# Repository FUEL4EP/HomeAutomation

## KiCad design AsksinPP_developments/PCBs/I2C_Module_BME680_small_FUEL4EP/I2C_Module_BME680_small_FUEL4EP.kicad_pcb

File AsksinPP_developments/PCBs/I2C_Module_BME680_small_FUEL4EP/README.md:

# I2C_Module_BME680_small_FUEL4EP  

## kleine I2C BME680 VOC Sensor Aufsteckplatine für DIY AsksinPP-Projekte

- basierend auf [Bosch BME680](https://www.bosch-sensortec.com/media/boschsensortec/downloads/datasheets/bst-bme680-ds001.pdf)
- passend zu den folgenden Mutterplatinen:
	* [HB_Stamp_ATMega1284P_FUEL4EP](https://github.com/FUEL4EP/HomeAutomation/tree/master/AsksinPP_developments/PCBs/HB_Stamp_ATMega1284P_FUEL4EP)	
- VCC max. ist 3,3 Volt !!
- die voreingestellte Standard-I2C-Adresse ist 0x76
- für die I2C-Adresse 0x77 ist der Jumper JP2 aufzutrennen und der Jumper JP1 mit Lötzinn zu überbrücken

- Infos zu AsksinPP sind [hier](https://asksinpp.de) und [hier](https://asksinpp.de/Grundlagen/01_hardware.html#verdrahtung) zu finden

## Platinenmaße

- Breite: 14,08 mm
- Weite: 17 mm
- Platinendicke 1,6 mm (bei der Bestellung bei JLCPCB auswählen)

## Stromlaufplan

- ist [hier](./Schematics/I2C_Module_BME680_small_FUEL4EP.pdf)

## Status

- die Platine V1.0 wurde bei JLCPCB gefertigt und mit dem Sketch [HB-UNI-SENSOR1-AQ-BME680_KF_rLF](https://github.com/FUEL4EP/HomeAutomation/tree/master/AsksinPP_developments/sketches/HB-UNI-Sensor1-AQ-BME680_KF_rLF) validiert:

## Rückmeldungen

- und Verbesserungsvorschläge sind willkommen.

### KiCAD Plugin
- für die Erzeugung der JLCPCB Produktionsdaten wurde das Plugin [KiCAD JLCPCB tools](https://github.com/bouni/kicad-jlcpcb-tools) verwendet.

## Daten für die Bestellung bei JLCPCB

- die Daten für die Bestellung liegen im Verzeichnis [./jlcpcb/production_files/](./jlcpcb/production_files/)
- Gerber-Daten als Zip-Datei
- BOM- und CPL-Daten als CSV-Datei

## lokale Installation des Github Releases auf Deinem Computer

- gehe bitte in Dein Zielinstallationsverzeichnis, wo Du mit der I2C_Module_BME680_small_FUEL4EP Platine mit KiCAD arbeiten möchtest

  - gebe dort 'git clone https://github.com/FUEL4EP/HomeAutomation.git' ein
	  + damit lädst Du mein [Sammelrepository](https://github.com/FUEL4EP/HomeAutomation) für alle meine auf Github freigegebenen HomeBrew Entwicklungen herunter.
  - dann findest Du ein neues Verzeichnis 'HomeAutomation' auf Deinem Rechner, das alle meine auf Github freigebenen Entwicklungen enthält, siehe [README.md](https://github.com/FUEL4EP/HomeAutomation/blob/master/README.md)
  	+ mache bitte regelmäßig ein Update mit 'git pull'
 -	die Platine I2C_Module_BME680_small_FUEL4EP findest Du unter './HomeAutomation/tree/master/AsksinPP_developments/PCBs/I2C_Module_BME680_small_FUEL4EP'
 
- alternativ kann vom Github [Sammelrepository](https://github.com/FUEL4EP/HomeAutomation) die ZIP-Datei HomeAutomation-master.zip heruntergeladen und auf dem lokalen Rechner ausgepackt werden. Bitte dann regelmäßig auf Github nach Updates schauen.

## Versionsverlauf

- V1.0   29. Sep 2024: Initiale Veröffentlichung auf Github
- L V1.1 30. Sep 2024: Verbesserte Platzierung von C3
- KiCad Schaltplan-Editor Version: 8.0.5-8.0.5-0~ubuntu22.04.1, release build
 unter Kubuntu22.04.4
- KiCad Leiterplatteneditor Version: 8.0.5-8.0.5-0~ubuntu22.04.1, release build
 unter Kubuntu22.04.4
- PCB Version 1.1
- Schematics  1.0

## Sammelbestellung

- wer Interesse an einer gemeinsamen Bestellung von Platinen und/oder Gehäusen bei JLCPCB hat, fragt bitte per per PN bei bei [FUEL4EP](https://homematic-forum.de/forum/ucp.php?i=pm&mode=compose&u=20685) an.
- wenn genügend Interesse (>= 20 bestückte Platinen und/oder 3D gedruckten Gehäusen) zustande kommt, biete ich an, Platinen  und Gehäuse gegen Vorkasse per PayPal zum Selbstkostenpreis + Versandkosten + 3 Euro Aufwandspauschale pro Versand zum Besteller bei JLCPCB zu bestellen und dann weiterzuverkaufen. Vor einer Bestellung wird ein Angebot bei JLCPCB eingeholt und an die Interessenten zur Zustimmung verteilt.

## Disclaimer

-   die Nutzung der hier veröffentlichten Inhalte erfolgt vollständig auf eigenes Risiko und ohne jede Gewähr.

## Lizenz 

**Creative Commons BY-NC-SA**<br>
Give Credit, NonCommercial, ShareAlike

<br />This work is licensed under a <a rel="license" href="http://creativecommons.org/licenses/by-nc-sa/4.0/">Creative Commons Attribution-NonCommercial-ShareAlike 4.0 International License</a>.

-EOF

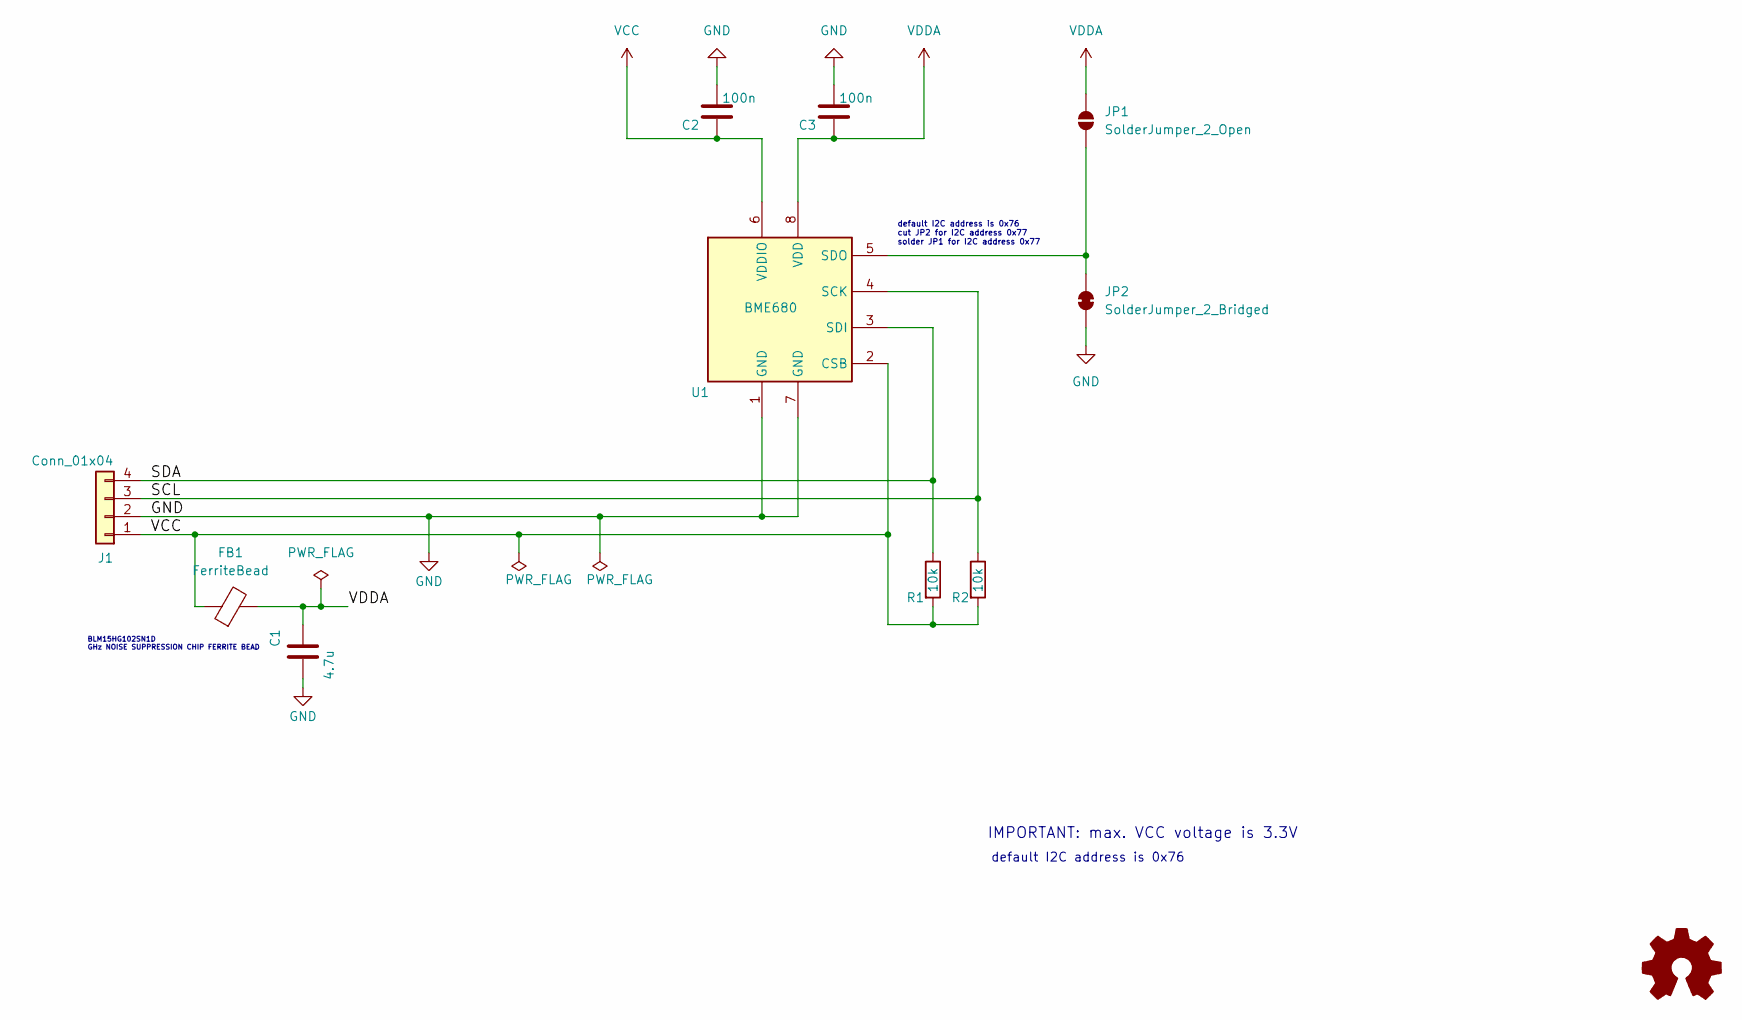
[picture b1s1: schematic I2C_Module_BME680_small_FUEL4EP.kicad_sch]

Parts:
C1: 4.7u; C_0603_1608Metric; LCSC C19666
C2, C3: 100n; C_0603_1608Metric; LCSC C14663
FB1: FerriteBead; L_0402_1005Metric; LCSC C76889
J1: Conn_01x04; PinHeader_1x04_P2.54mm_Vertical
JP1: SolderJumper_2_Open; SolderJumper-2_P1.3mm_Open_Pad1.0x1.5mm
JP2: SolderJumper_2_Bridged; SolderJumper-2_P1.3mm_Bridged_Pad1.0x1.5mm
LOGO1: Logo_Open_Hardware_Small; CC-BY-ND-SA
R1, R2: 10k; R_0402_1005Metric; LCSC C25744
U1: BME680; Bosch_LGA-8_3x3mm_P0.8mm_ClockwisePinNumbering; LCSC C125972

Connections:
/SCL: J1.3, R2.1, U1.4 (SCK)
/SDA: J1.4, R1.1, U1.3 (SDI)
GND: C1.2, C2.1, C3.1, J1.2, JP2.1 (A), U1.1 (GND), U1.7 (GND)
unnamed: JP1.1 (A), JP2.2 (B), U1.5 (SDO)
VCC: C2.2, FB1.1, J1.1, R1.2, R2.2, U1.2 (CSB), U1.6 (VDDIO)
VDDA: C1.1, C3.2, FB1.2, JP1.2 (B), U1.8 (VDD)

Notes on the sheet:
cut JP2 for I2C address 0x77
default I2C address is 0x76
IMPORTANT: max. VCC voltage is 3.3V
solder JP1 for I2C address 0x77
BLM15HG102SN1D GHz NOISE SUPPRESSION CHIP FERRITE BEAD

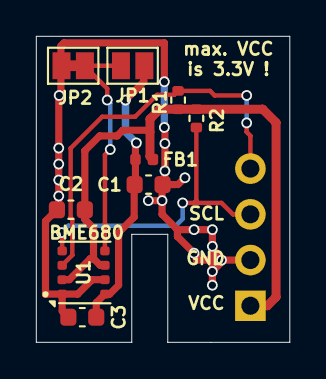
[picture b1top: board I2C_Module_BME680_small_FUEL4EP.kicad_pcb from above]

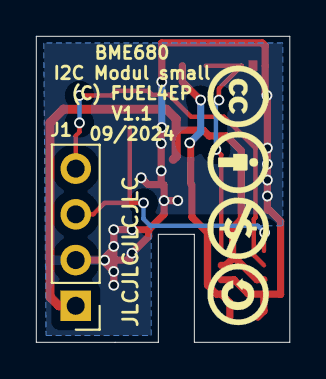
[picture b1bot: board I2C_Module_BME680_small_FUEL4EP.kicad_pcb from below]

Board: 2 copper layers, 14.1 x 17.0 mm, 11 parts (2 on the bottom side), 6 nets.

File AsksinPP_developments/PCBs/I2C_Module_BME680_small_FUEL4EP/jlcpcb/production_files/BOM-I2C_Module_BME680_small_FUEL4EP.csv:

Comment,Designator,Footprint,LCSC,Quantity
BME680,U1,Bosch_LGA-8_3x3mm_P0.8mm_ClockwisePinNumbering,C125972,1
100n,"C2,C3",C_0603_1608Metric,C14663,2
4.7u,C1,C_0603_1608Metric,C19666,1
10k,"R1,R2",R_0402_1005Metric,C25744,2
FerriteBead,FB1,L_0402_1005Metric,C76889,1

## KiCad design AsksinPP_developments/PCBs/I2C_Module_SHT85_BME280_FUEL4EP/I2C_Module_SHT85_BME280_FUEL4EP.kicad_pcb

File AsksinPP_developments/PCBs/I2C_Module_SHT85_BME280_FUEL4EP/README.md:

# I2C_Module_SHT85_BME280_FUEL4EP  

# Warnung: Diese Version der Platine ist noch nicht valdiert. Nutzung auf eigenes Risiko!

## I2C SHT85 und BME280 Sensor Aufsteckplatine für DIY AsksinPP-Projekte

- basierend auf [Sensirion SHT85](https://sensirion.com/media/documents/4B40CEF3/61642381/Sensirion_Humidity_Sensors_SHT85_Datasheet.pdf) für die genaue Temperatur- und Luftfeuchtemessung
- basierend auf [Bosch BME280](https://www.bosch-sensortec.com/media/boschsensortec/downloads/datasheets/bst-bme280-ds002.pdf) für die Luftdruckmessung

- passend zu den folgenden Mutterplatinen:
	* [HB-UNI-SEN-BATT_ATMega1284P_E07-868MS10_FUEL4EP](https://github.com/FUEL4EP/HomeAutomation/tree/master/AsksinPP_developments/PCBs/HB-UNI-SEN-BATT_ATMega1284P_E07-868MS10_FUEL4EP)
	* [HB-UNI-SEN-BATT_ATMega1284P_E07-868MS10_FRAM_FUEL4EP](https://github.com/FUEL4EP/HomeAutomation/tree/master/AsksinPP_developments/PCBs/HB-UNI-SEN-BATT_ATMega1284P_E07-868MS10_FRAM_FUEL4EP)
	* [HB-UNI-SEN-BATT_FUEL4EP](https://github.com/FUEL4EP/HomeAutomation/tree/master/AsksinPP_developments/PCBs/HB-UNI-SEN-BATT_FUEL4EP)
	* [HB-UNI-SEN-BATT_ATMega1284P_E07-868MS10_FUEL4EP](https://github.com/FUEL4EP/HomeAutomation/tree/master/AsksinPP_developments/PCBs/HB-UNI-SEN-BATT_ATMega1284P_E07-868MS10_FUEL4EP)
	* Befestigung mit 2 Stiftleisten J1 und J2 auf die Mutterplatine
	* [kurze Stiftleiste mit Höhe 6,5 mm verwenden](https://cdn-reichelt.de/documents/datenblatt/C700/WP952-08-004-1-00_DB-DE.pdf) z.B. bei [Reichelt](https://www.reichelt.de/stiftleiste-rm-2-54mm-gerade-1-reihig-4-polig-w-p-952-084-1-p331040.html?&trstct=pol_10&nbc=1), da der SHT85 Sensor senkrecht eingebaut wird
	
- VCC max. ist 3,3 Volt !!
- die voreingestellte Standard-I2C-Adresse des BME280 Sensors ist 0x76
- für die I2C-Adresse 0x77 des BME280 Sensors ist der Jumper JP1 aufzutrennen und der Jumper JP2 mit Lötzinn zu überbrücken
- die voreingestellte I2C-Adresse des SHT85 Sensors ist 0x44

- Infos zu AsksinPP sind [hier](https://asksinpp.de) und [hier](https://asksinpp.de/Grundlagen/01_hardware.html#verdrahtung) zu finden

## Platinenmaße

- Breite: 30,48 mm
- Weite: 17 mm
- Platinendicke 1,6 mm (bei der Bestellung bei JLCPCB auswählen)

## Stromlaufplan

- ist [hier](./Schematics/I2C_Module_SHT85_BME280_FUEL4EP.pdf)

## Status

- diese Platine wurde noch nicht bei JLCPCB gefertigt und ist daher auch nicht validiert. Nutzung auf eigenes Risiko!

## Rückmeldungen

- und Verbesserungsvorschläge sind willkommen.

### KiCAD Plugin
- für die Erzeugung der JLCPCB Produktionsdaten wurde das Plugin [KiCAD JLCPCB tools](https://github.com/bouni/kicad-jlcpcb-tools) verwendet.

## Daten für die Bestellung bei JLCPCB

- die Daten für die Bestellung liegen im Verzeichnis [./jlcpcb/production_files/](./jlcpcb/production_files/)
- Gerber-Daten als Zip-Datei
- BOM- und CPL-Daten als CSV-Datei

- die Rotation von U1 (BME280) ist bei der Plazierungsprüfansicht von JLCPCB  falsch und muss händisch korrigiert und geprüft werden. Bitte die entsprechende Option 'Confirm Parts Placement'  beim Bestellen wählen.

## lokale Installation des Github Releases auf Deinem Computer

- gehe bitte in Dein Zielinstallationsverzeichnis, wo Du mit der I2C_Module_SHT85_BME280_FUEL4EP Platine mit KiCAD arbeiten möchtest

  - gebe dort 'git clone https://github.com/FUEL4EP/HomeAutomation.git' ein
	  + damit lädst Du mein [Sammelrepository](https://github.com/FUEL4EP/HomeAutomation) für alle meine auf Github freigegebenen HomeBrew Entwicklungen herunter.
  - dann findest Du ein neues Verzeichnis 'HomeAutomation' auf Deinem Rechner, das alle meine auf Github freigebenen Entwicklungen enthält, siehe [README.md](https://github.com/FUEL4EP/HomeAutomation/blob/master/README.md)
  	+ mache bitte regelmäßig ein Update mit 'git pull'
 -	die Platine I2C_Module_SHT85_BME280_FUEL4EP findest Du unter './HomeAutomation/tree/master/AsksinPP_developments/PCBs/I2C_Module_SHT85_BME280_FUEL4EP'
 
- alternativ kann vom Github [Sammelrepository](https://github.com/FUEL4EP/HomeAutomation) die ZIP-Datei HomeAutomation-master.zip heruntergeladen und auf dem lokalen Rechner ausgepackt werden. Bitte dann regelmäßig auf Github nach Updates schauen.

## Versionsverlauf

-   V1.0 08. Sep 2023: Initiale Veröffentlichung auf Github
-	V1.1 15. Dez 2023: korrigierte Positionierung der Stiftleisten in 3D Ansicht
-	V1.2 08. Feb 2024: Fix der I2C Pull-Up Widerstände
-	S V1.3 16. Apr 2024: Ersetzen von R3 durch JP2 wegen Ruhestrom; Migration auf KiCAD 7
-	L V1.3 16. Apr 2024: Ersetzen von R3 durch JP2 wegen Ruhestrom; Migration auf KiCAD 7
-	S V1.4 30. Sep 2024: Migration auf KiCAD 8
-	L V1.4 30. Sep 2024: Migration auf KiCAD 8; Fix von DRC Regeln
- KiCad Schaltplan-Editor Version: 8.0.5-8.0.5-0~ubuntu22.04.1, release build unter Kubuntu22.04.4
- KiCad Leiterplatteneditor Version: 8.0.5-8.0.5-0~ubuntu22.04.1, release build unter Kubuntu22.04.4
- PCB Version 1.4
- Schematics  1.4

## Disclaimer

-   die Nutzung der hier veröffentlichten Inhalte erfolgt vollständig auf eigenes Risiko und ohne jede Gewähr.

## Lizenz 

**Creative Commons BY-NC-SA**<br>
Give Credit, NonCommercial, ShareAlike

<br />This work is licensed under a <a rel="license" href="http://creativecommons.org/licenses/by-nc-sa/4.0/">Creative Commons Attribution-NonCommercial-ShareAlike 4.0 International License</a>.

-EOF

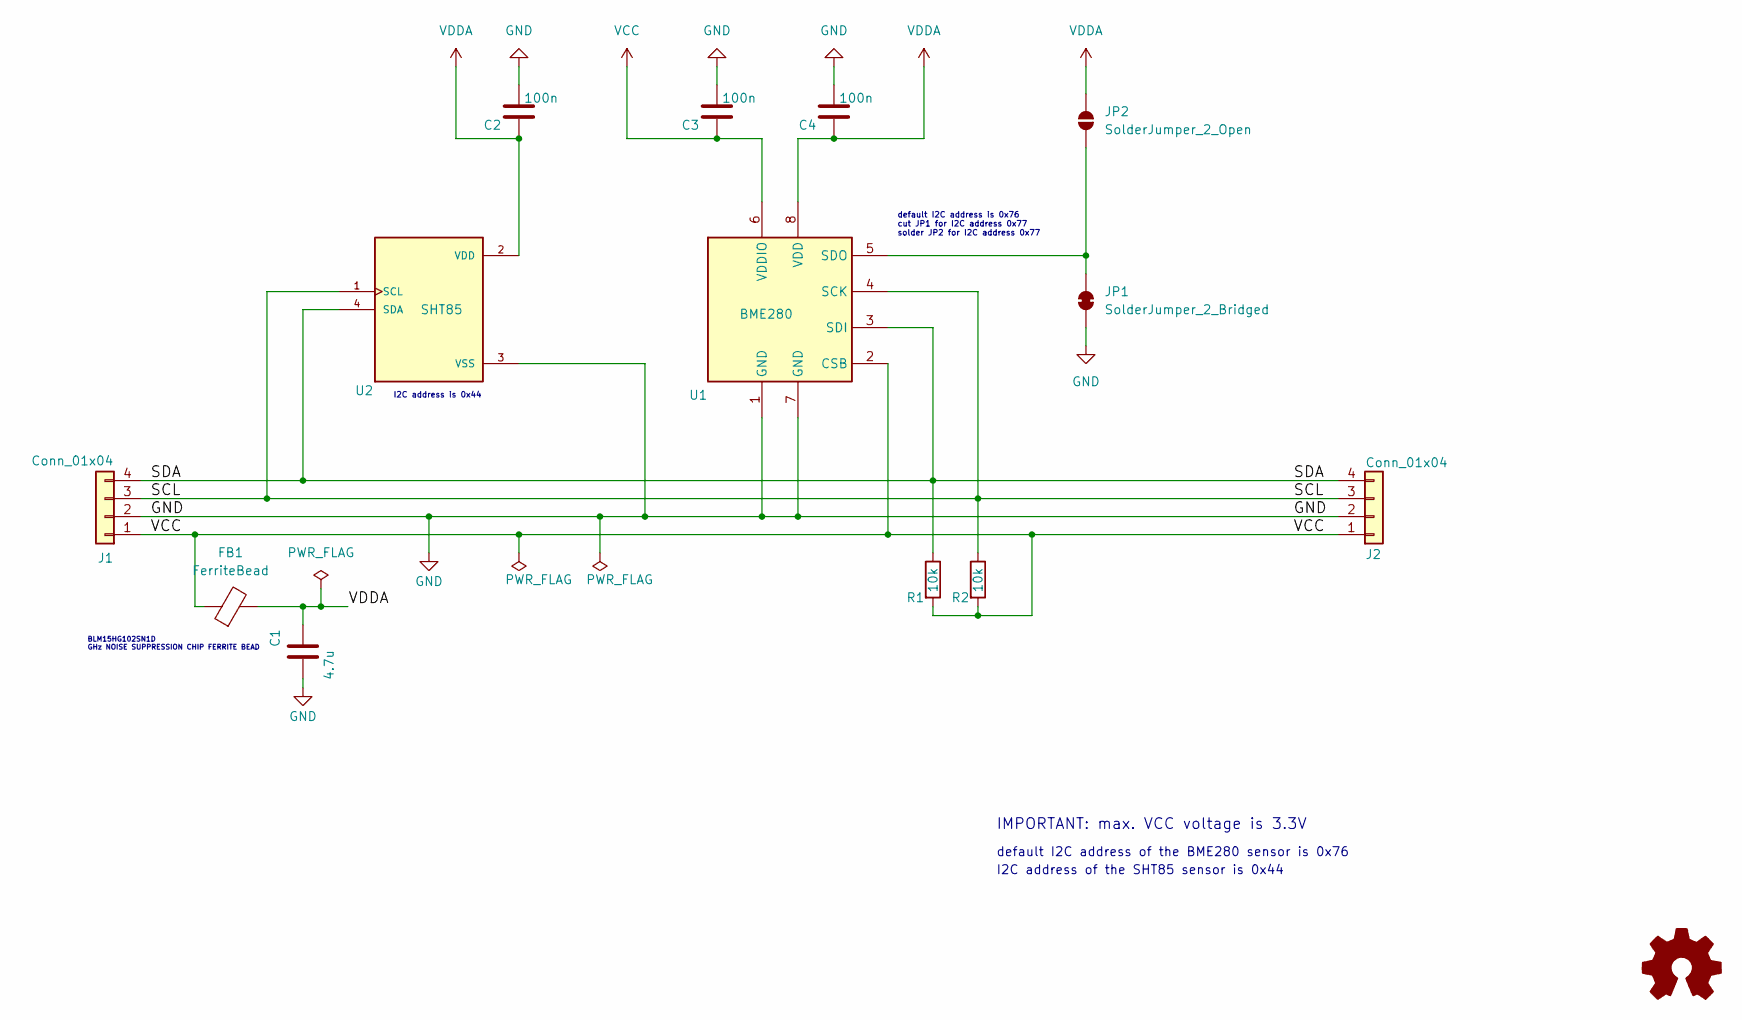
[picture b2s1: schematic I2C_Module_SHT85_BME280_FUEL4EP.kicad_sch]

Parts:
C1: 4.7u; C_0603_1608Metric; LCSC C19666
C2, C3, C4: 100n; C_0603_1608Metric; LCSC C14663
FB1: FerriteBead; L_0402_1005Metric; LCSC C76889
J1, J2: Conn_01x04; PinHeader_1x04_P2.54mm_Vertical
JP1: SolderJumper_2_Bridged; SolderJumper-2_P1.3mm_Bridged_Pad1.0x1.5mm
JP2: SolderJumper_2_Open; SolderJumper-2_P1.3mm_Open_Pad1.0x1.5mm
LOGO1: Logo_Open_Hardware_Small; CC-BY-ND-SA
R1, R2: 10k; R_0402_1005Metric; LCSC C25744
U1: BME280; Bosch_LGA-8_2.5x2.5mm_P0.65mm_ClockwisePinNumbering; LCSC C92489
U2: SHT85; XDCR_SHT85; LCSC C779800

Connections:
/SCL: J1.3, J2.3, R2.1, U1.4 (SCK), U2.1 (SCL)
/SDA: J1.4, J2.4, R1.1, U1.3 (SDI), U2.4 (SDA)
GND: C1.2, C2.1, C3.1, C4.1, J1.2, J2.2, JP1.1 (A), U1.1 (GND), U1.7 (GND), U2.3 (VSS)
unnamed: JP1.2 (B), JP2.1 (A), U1.5 (SDO)
VCC: C3.2, FB1.1, J1.1, J2.1, R1.2, R2.2, U1.2 (CSB), U1.6 (VDDIO)
VDDA: C1.1, C2.2, C4.2, FB1.2, JP2.2 (B), U1.8 (VDD), U2.2 (VDD)

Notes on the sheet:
cut JP1 for I2C address 0x77
I2C address is 0x44
BLM15HG102SN1D GHz NOISE SUPPRESSION CHIP FERRITE BEAD
solder JP2 for I2C address 0x77
default I2C address of the BME280 sensor is 0x76
I2C address of the SHT85 sensor is 0x44
default I2C address is 0x76
IMPORTANT: max. VCC voltage is 3.3V

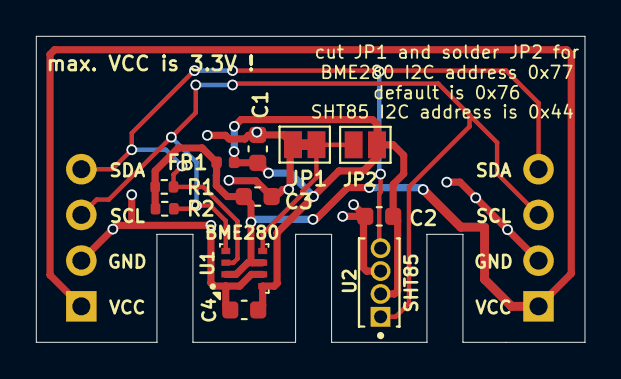
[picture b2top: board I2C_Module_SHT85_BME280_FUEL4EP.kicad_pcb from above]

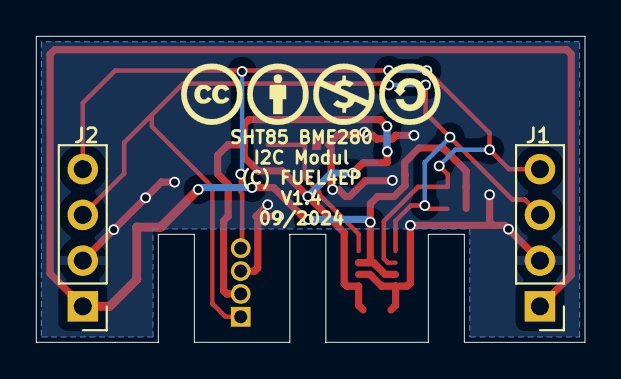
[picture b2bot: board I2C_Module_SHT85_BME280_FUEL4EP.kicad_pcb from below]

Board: 2 copper layers, 30.5 x 17.0 mm, 14 parts (3 on the bottom side), 6 nets.

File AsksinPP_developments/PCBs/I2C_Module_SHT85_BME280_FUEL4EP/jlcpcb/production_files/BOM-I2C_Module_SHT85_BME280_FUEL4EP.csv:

Comment,Designator,Footprint,LCSC
100n,"C2,C3,C4",C_0603_1608Metric,C14663
4.7u,C1,C_0603_1608Metric,C19666
10k,"R1,R2",R_0402_1005Metric,C25744
FerriteBead,FB1,L_0402_1005Metric,C76889
SHT85,U2,XDCR_SHT85,C779800
BME280,U1,Bosch_LGA-8_2.5x2.5mm_P0.65mm_ClockwisePinNumbering,C92489

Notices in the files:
AsksinPP_developments/PCBs/I2C_Module_BME680_small_FUEL4EP/I2C_Module_BME680_small_FUEL4EP.kicad_sch:
Creative Commons License, non-commercial
AsksinPP_developments/PCBs/I2C_Module_BME680_small_FUEL4EP/README.md:
License: CC BY-NC-SA 4.0
